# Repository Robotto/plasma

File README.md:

Interfacing a plasma VU meter from the past with an ESP8266 on a Wemos D1 mini board.

This is highly experimental, dangerous, and possibly fun.

[Interactive BOM here](https://htmlpreview.github.io/?https://github.com/robotto/plasma/blob/master/bom/ibom.html).

[OH! And check out KiCanvas!](https://kicanvas.org/?github=https%3A%2F%2Fgithub.com%2FRobotto%2Fplasma)

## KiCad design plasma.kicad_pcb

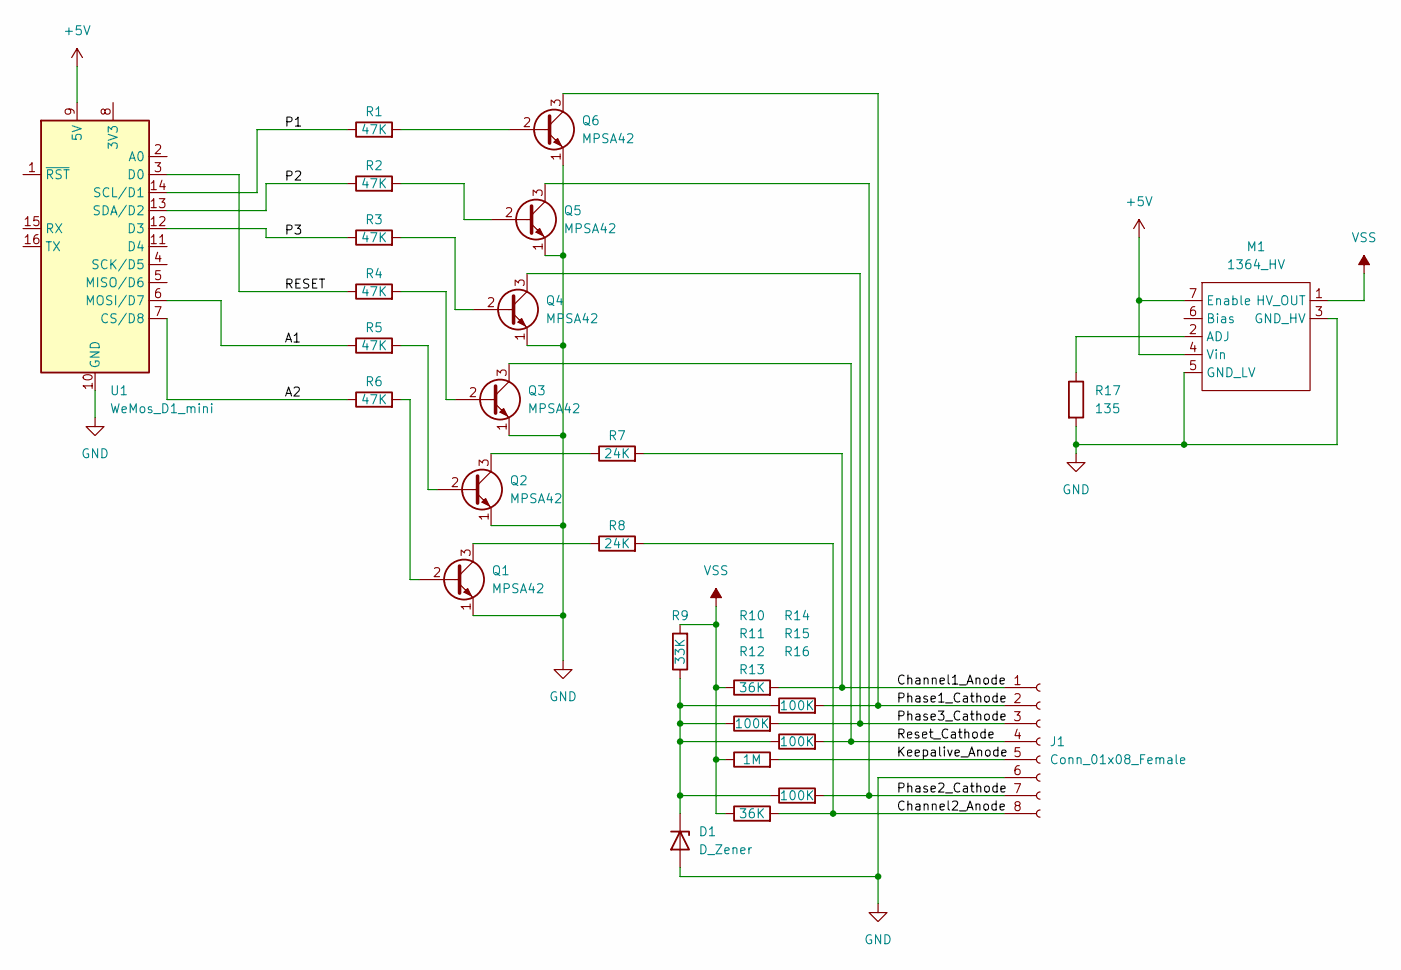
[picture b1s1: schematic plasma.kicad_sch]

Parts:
D1: D_Zener; R_Axial_DIN0207_L6.3mm_D2.5mm_P7.62mm_Horizontal
J1: Conn_01x08_Female; PinHeader_1x08_P2.54mm_Horizontal
M1: 1364_HV
Q1, Q2, Q3, Q4, Q5, Q6: MPSA42; TO-92_Inline
R1, R2, R3, R4, R5, R6: 47K; R_Axial_DIN0207_L6.3mm_D2.5mm_P7.62mm_Horizontal
R7, R8: 24K; R_Axial_DIN0207_L6.3mm_D2.5mm_P7.62mm_Horizontal
R9: 33K; R_Axial_DIN0207_L6.3mm_D2.5mm_P7.62mm_Horizontal
R10, R13: 36K; R_Axial_DIN0207_L6.3mm_D2.5mm_P7.62mm_Horizontal
R11, R14, R15, R16: 100K; R_Axial_DIN0207_L6.3mm_D2.5mm_P7.62mm_Horizontal
R12: 1M; R_Axial_DIN0207_L6.3mm_D2.5mm_P7.62mm_Horizontal
R17: 135; R_Axial_DIN0207_L6.3mm_D2.5mm_P7.62mm_Horizontal
U1: WeMos_D1_mini; WEMOS_D1_mini_light

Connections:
+5V: M1.4 (Vin), M1.7 (Enable), U1.9 (5V)
/A1: R5.1, U1.6 (MOSI/D7)
/A2: R6.1, U1.7 (CS/D8)
/Channel1_Anode: J1.1, R7.2, R10.2
/Channel2_Anode: J1.8, R8.2, R13.2
/Keepalive_Anode: J1.5, R12.2
/P1: R1.1, U1.14 (SCL/D1)
/P2: R2.1, U1.13 (SDA/D2)
/P3: R3.1, U1.12 (D3)
/Phase1_Cathode: J1.2, Q6.3 (C), R14.2
/Phase2_Cathode: J1.7, Q5.3 (C), R16.2
/Phase3_Cathode: J1.3, Q4.3 (C), R11.2
/RESET: R4.1, U1.3 (D0)
/Reset_Cathode: J1.4, Q3.3 (C), R15.2
GND: D1.2 (A), J1.6, M1.3 (GND_HV), M1.5 (GND_LV), Q1.1 (E), Q2.1 (E), Q3.1 (E), Q4.1 (E), Q5.1 (E), Q6.1 (E), R17.2, U1.10 (GND)
unnamed: D1.1 (K), R9.1, R11.1, R14.1, R15.1, R16.1
unnamed: M1.2 (ADJ), R17.1
unnamed: Q1.2 (B), R6.2
unnamed: Q1.3 (C), R8.1
unnamed: Q2.2 (B), R5.2
unnamed: Q2.3 (C), R7.1
unnamed: Q3.2 (B), R4.2
unnamed: Q4.2 (B), R3.2
unnamed: Q5.2 (B), R2.2
unnamed: Q6.2 (B), R1.2
VSS: M1.1 (HV_OUT), R9.2, R10.1, R12.1, R13.1

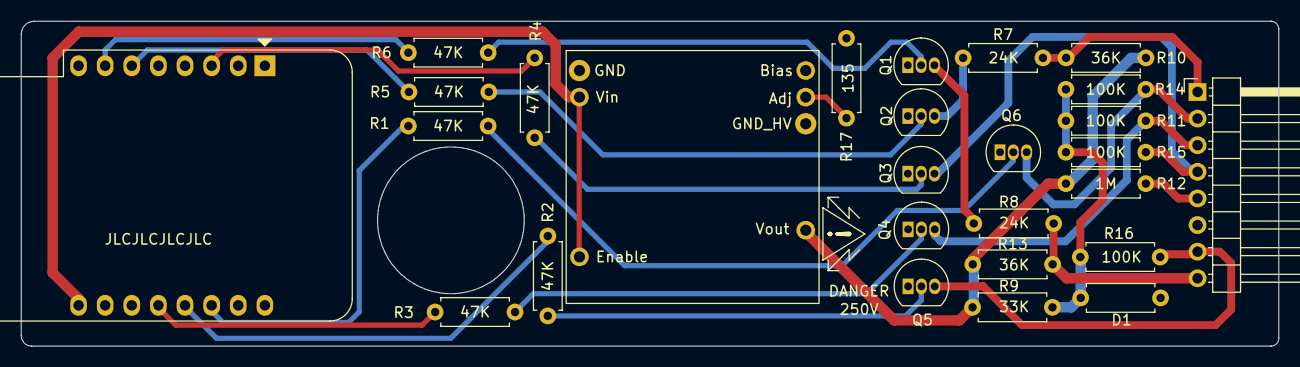
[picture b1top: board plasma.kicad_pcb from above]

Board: 2 copper layers, 120.0 x 31.0 mm, 27 parts (0 on the bottom side), 26 nets.

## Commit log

2023-03-09 git init
2023-03-09 playing the routing game
2023-03-11 added plasma vu-meter dimensions. trying to match them to the board
2023-03-13 moved the hole, made some gerbers
2023-03-14 rounded PCB corners
2023-03-14 updated gerbers
2023-03-14 added interactive bom, generated by awesome plugin.
2023-03-14 added README with link to ibom
2023-03-28 safety commit
2023-03-28 Still not running, but getting closer...
2023-10-19 Still not entirely working... gonna try something else soon.
2023-10-20 New thing
    Testing timing from http://www.aartsite.nl/2023/10/06/burroughs-bargraph-display/
2023-10-20 Rework new timing to match hw pinout
2023-10-21 Oh my god, my code was fine, except for wrong pinout :D
2023-10-21 yeeeet
2023-10-21 haaaaands
2023-10-21 fresher than before
2023-10-22 Added fancy sine/cosine animations, and calibrated mininum and maximum values for the plasma to look AMAZING
2023-10-22 just a bit of spiffing up the code
2023-10-22 not sure i changed anything here...
2023-10-23 fine-tuning routing
2023-10-24 renamed file
